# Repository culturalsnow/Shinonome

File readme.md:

Shinonome
===

38-key columnar stagger keyboard inspired by the Mitosis, Chimera Ergo, Corne and Comet46.

Keyboard Maintainer: [Cultural Snow](https://github.com/culturalsnow/) / [@SA_EndlessGame](https://twitter.com/SA_EndlessGame)  
Hardware Supported: Shinonome PCB  
Hardware Availability: (https://twitter.com/SA_EndlessGame)

Make example for this keyboard (after setting up your build environment):

    make shinonome:default

See the [build environment setup](https://docs.qmk.fm/#/getting_started_build_tools) and the [make instructions](https://docs.qmk.fm/#/getting_started_make_guide) for more information. Brand new to QMK? Start with our [Complete Newbs Guide](https://docs.qmk.fm/#/newbs).

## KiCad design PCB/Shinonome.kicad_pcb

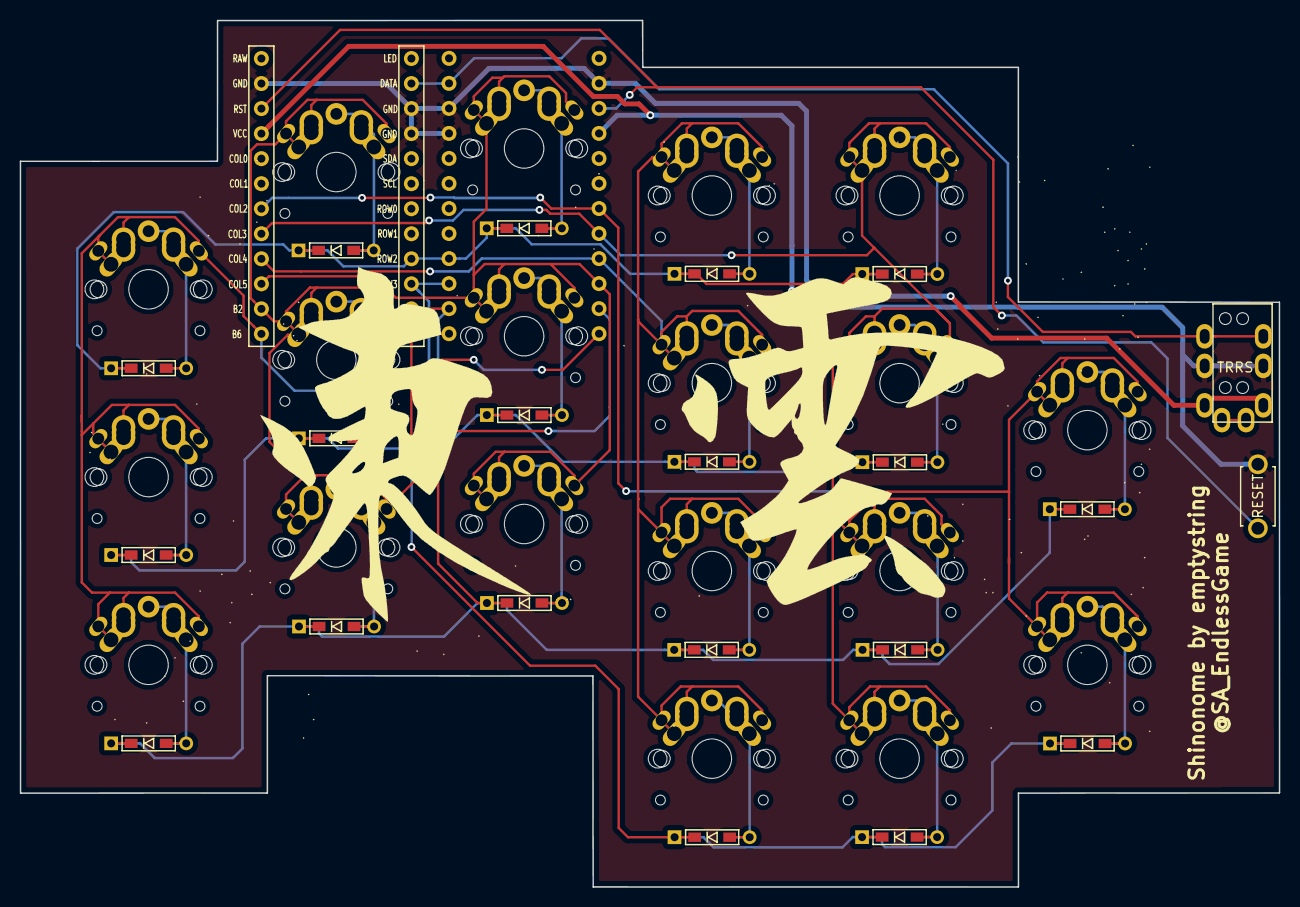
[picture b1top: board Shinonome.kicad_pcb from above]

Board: 2 copper layers, 127.7 x 87.9 mm, 42 parts (1 on the bottom side), 33 nets.

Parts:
D1, D2, D3, D4, D5, D6, D7, D8, D9, D10, D11, D12, D13, D14, D15, D16, D17, D18, D19: D; D3_TH_SMD
J1: MJ-4PP-9
SW1, SW2, SW3, SW4, SW5, SW6, SW7, SW8, SW9, SW10, SW11, SW12, SW13, SW14, SW15, SW16, SW17, SW18, SW19: SW_PUSH; MX_ALPS_PG1350_noLed
SW20: reset; ResetSW
U1, U2: ProMicro; ProMicro_v2_Backside

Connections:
GND: J1.C, SW20.2, U1.3, U1.4, U1.23, U2.3, U2.4, U2.23
unnamed: D1.2, SW1.2
unnamed: D2.2, SW2.2
unnamed: D3.2, SW3.2
unnamed: D4.2, SW4.2
unnamed: D5.2, SW5.2
unnamed: D6.2, SW6.2
unnamed: D7.2, SW7.2
unnamed: D8.2, SW8.2
unnamed: D9.2, SW9.2
unnamed: D10.2, SW10.2
unnamed: D11.2, SW11.2
unnamed: D12.2, SW12.2
unnamed: D13.2, SW13.2
unnamed: D14.2, SW14.2
unnamed: D15.2, SW15.2
unnamed: D16.2, SW16.2
unnamed: D17.2, SW17.2
unnamed: D18.2, SW18.2
unnamed: D19.2, SW19.2
VCC: J1.D, U1.21, U2.21
col0: SW1.1, SW2.1, SW3.1, U1.13, U2.13
col1: SW4.1, SW5.1, SW6.1, U1.14, U2.14
col2: SW7.1, SW8.1, SW9.1, U1.15, U2.15
col3: SW10.1, SW11.1, SW12.1, SW13.1, U1.16, U2.16
col4: SW14.1, SW15.1, SW16.1, SW17.1, U1.17, U2.17
col5: SW18.1, SW19.1, U1.18, U2.18
data: J1.B, U1.2, U2.2
reset: SW20.1, U1.22, U2.22
row0: D1.1, D4.1, D7.1, D10.1, D14.1, U1.9, U2.9
row1: D2.1, D5.1, D8.1, D11.1, D15.1, U1.10, U2.10
row2: D3.1, D6.1, D9.1, D12.1, D16.1, D18.1, U1.11, U2.11
row3: D13.1, D17.1, D19.1, U1.12, U2.12

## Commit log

2019-02-02 20190202 first commit
2019-02-02 changed directory hierarchy
2019-02-02 added dxf file
2019-02-04 new dxf file
2019-02-05 first pass pcb complete
2019-02-05 added images
2019-02-05 rename image
2019-02-07 firmware first draft
2019-02-13 added logos and removed confusing warning from PM footprint
2019-02-18 gerber created
2019-03-05 fixed trrs jack incorrect pins
2019-03-05 added logos and regenerated gerber
